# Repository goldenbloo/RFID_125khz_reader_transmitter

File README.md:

# RFID_125khz_reader_transmitter
Implementation of a 125 kHz RFID tag reader and transmitter. It utilizes the EM4100 protocol with Manchester encoding, using 64 cycles per bit.
The code is written in C for the Atmega8A and compiled using the avr-gcc compiler.<br>
The schematic is based on Vassilis Serasidis's project: <a href=https://www.serasidis.gr/circuits/RFID_reader/125kHz_RFID_reader.htm>125 kHz RFID Reader</a> <br>
The Manchester encoding algorithm is adopted from Atmel's application notes on Manchester encoding: <a href=https://ww1.microchip.com/downloads/en/AppNotes/Atmel-9164-Manchester-Coding-Basics_Application-Note.pdf>Atmel-9164 - Manchester Coding Basics.</a><br>
## Hardware
I used a coil from an RFID tag with an inductance of approximately 3.3 mH, paired with a 490 pF capacitor to achieve a resonant frequency of 125 kHz.<br> 
If you use a different coil or capacitor, be sure to create a resonant tank circuit.<br>
The transistors I used were any generic ones I could find on hand.
##

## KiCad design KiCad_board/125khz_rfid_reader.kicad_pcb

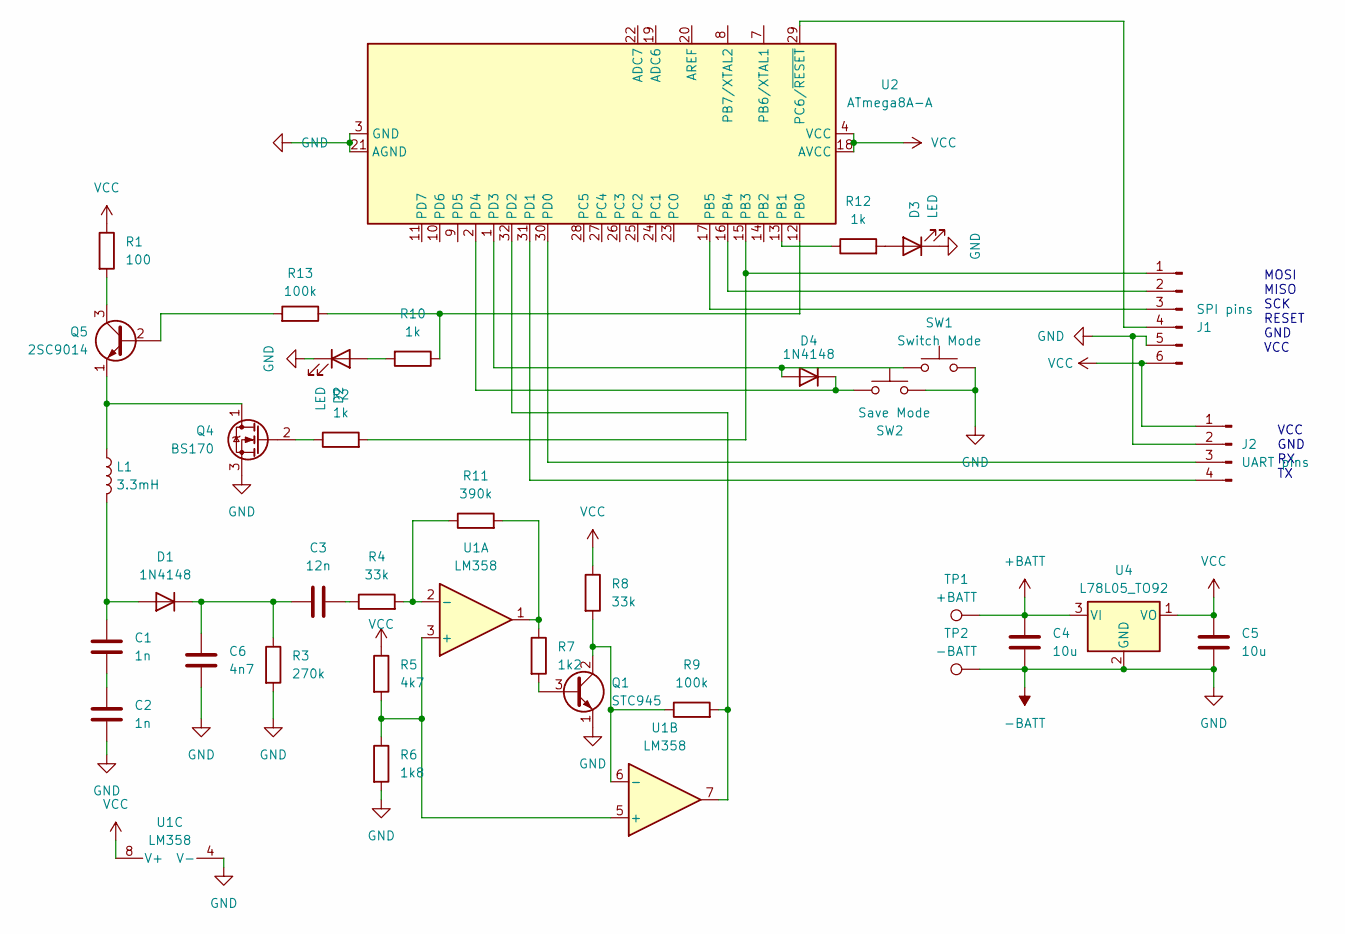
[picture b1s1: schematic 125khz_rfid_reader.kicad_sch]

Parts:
C1, C2: 1n; C_Disc_D5.0mm_W2.5mm_P5.00mm
C3: 12n; C_Disc_D5.0mm_W2.5mm_P5.00mm
C4, C5: 10u; CP_Radial_D6.3mm_P2.50mm
C6: 4n7; C_Disc_D5.0mm_W2.5mm_P5.00mm
D1, D4: 1N4148; D_DO-35_SOD27_P7.62mm_Horizontal
D2, D3: LED; LED_Rectangular_W5.0mm_H2.0mm
J1: SPI pins; PinHeader_1x06_P2.54mm_Vertical
J2: UART pins; PinHeader_1x04_P2.54mm_Vertical
L1: 3.3mH; L_Axial_L7.0mm_D3.3mm_P5.08mm_Vertical_Fastron_MICC
Q1: STC945; TO-92L_Inline_Wide
Q4: BS170; TO-92_Inline_Wide
Q5: 2SC9014; TO-92L_Inline_Wide
R1: 100; R_Axial_DIN0207_L6.3mm_D2.5mm_P10.16mm_Horizontal
R2, R10, R12: 1k; R_Axial_DIN0207_L6.3mm_D2.5mm_P10.16mm_Horizontal
R3: 270k; R_Axial_DIN0207_L6.3mm_D2.5mm_P10.16mm_Horizontal
R4, R8: 33k; R_Axial_DIN0207_L6.3mm_D2.5mm_P10.16mm_Horizontal
R5: 4k7; R_Axial_DIN0207_L6.3mm_D2.5mm_P10.16mm_Horizontal
R6: 1k8; R_Axial_DIN0207_L6.3mm_D2.5mm_P10.16mm_Horizontal
R7: 1k2; R_Axial_DIN0207_L6.3mm_D2.5mm_P10.16mm_Horizontal
R9, R13: 100k; R_Axial_DIN0207_L6.3mm_D2.5mm_P10.16mm_Horizontal
R11: 390k; R_Axial_DIN0207_L6.3mm_D2.5mm_P10.16mm_Horizontal
SW1: Switch Mode; SW_PUSH_6mm_H5mm
SW2: Save Mode; SW_PUSH_6mm_H5mm
TP1: +BATT; TestPoint_THTPad_D2.0mm_Drill1.0mm
TP2: -BATT; TestPoint_THTPad_D2.0mm_Drill1.0mm
U1: LM358; DIP-8_W7.62mm_LongPads
U2: ATmega8A-A; TQFP-32_7x7mm_P0.8mm
U4: L78L05_TO92; TO-92_Inline_Wide

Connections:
+BATT: C4.1, TP1.1, U4.3 (VI)
-BATT: C2.2, C4.2, C5.2, C6.2, D2.1 (K), D3.1 (K), J1.5, J2.2, Q1.1 (E), Q4.3 (S), R3.2, R6.2, SW1.2, SW2.2, TP2.1, U1.4 (V-), U2.3 (GND), U2.5 (GND), U2.21 (AGND), U4.2 (GND)
unnamed: C1.2, C2.1
unnamed: C3.2, R4.1
unnamed: C1.1, D1.2 (A), L1.2
unnamed: C3.1, C6.1, D1.1 (K), R3.1
unnamed: D2.2 (A), R10.2
unnamed: D3.2 (A), R12.2
unnamed: D4.2 (A), SW1.1, U2.1 (PD3)
unnamed: D4.1 (K), SW2.1, U2.2 (PD4)
unnamed: J1.1, R2.2, U2.15 (PB3)
unnamed: J1.2, U2.16 (PB4)
unnamed: J1.3, U2.17 (PB5)
unnamed: J1.4, U2.29 (PC6/~RESET)
unnamed: J2.3, U2.30 (PD0)
unnamed: J2.4, U2.31 (PD1)
unnamed: Q1.3 (B), R7.2
unnamed: Q1.2 (C), R8.2, R9.1, U1.6 (-)
unnamed: L1.1, Q4.1 (D), Q5.1 (E)
unnamed: Q4.2 (G), R2.1
unnamed: Q5.2 (B), R13.2
unnamed: Q5.3 (C), R1.2
unnamed: R7.1, R11.2, U1.1
unnamed: R5.2, R6.1, U1.3 (+), U1.5 (+)
unnamed: R4.2, R11.1, U1.2 (-)
unnamed: R10.1, R13.1, U2.12 (PB0)
unnamed: R12.1, U2.13 (PB1)
unnamed: R9.2, U1.7, U2.32 (PD2)
VCC: C5.1, J1.6, J2.1, R1.1, R5.1, R8.1, U1.8 (V+), U2.4 (VCC), U2.6 (VCC), U2.18 (AVCC), U4.1 (VO)

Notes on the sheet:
VCC GND RX TX
MOSI MISO SCK RESET GND VCC

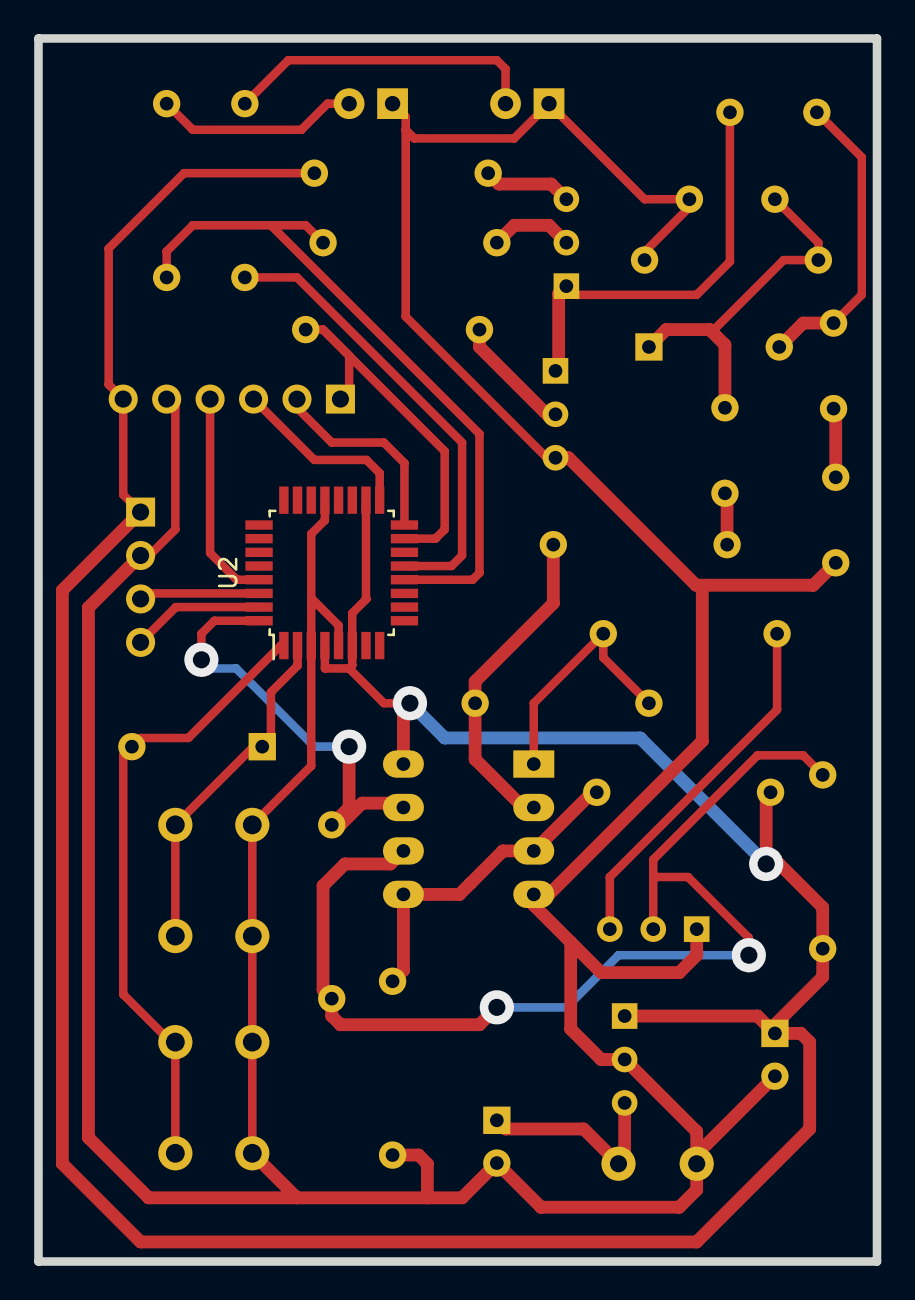
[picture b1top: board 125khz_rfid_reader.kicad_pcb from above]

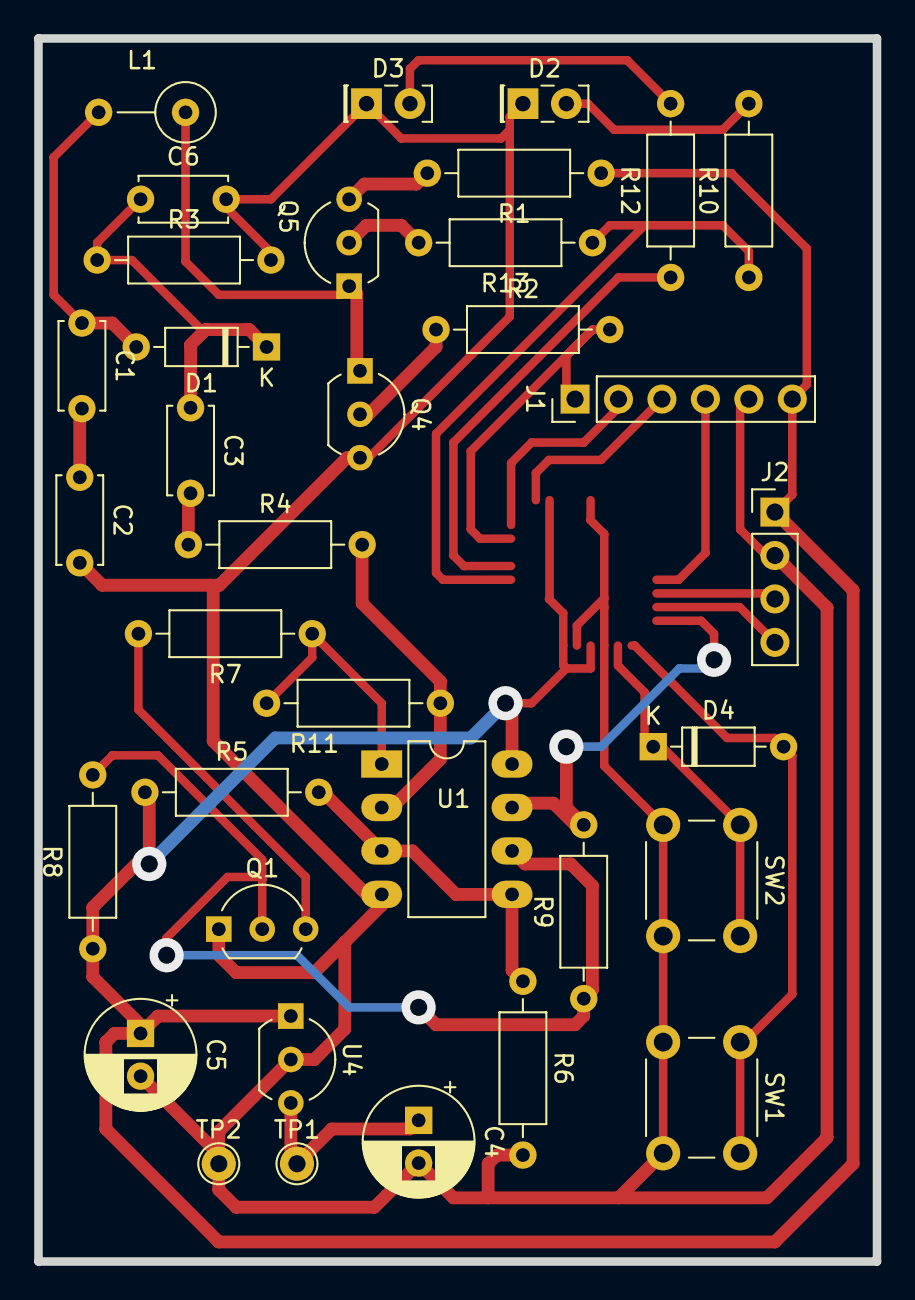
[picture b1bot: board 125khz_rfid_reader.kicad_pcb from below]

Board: 2 copper layers, 49.0 x 71.5 mm, 36 parts (35 on the bottom side), 29 nets.

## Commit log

2024-10-26 code added
2024-10-26 board added
